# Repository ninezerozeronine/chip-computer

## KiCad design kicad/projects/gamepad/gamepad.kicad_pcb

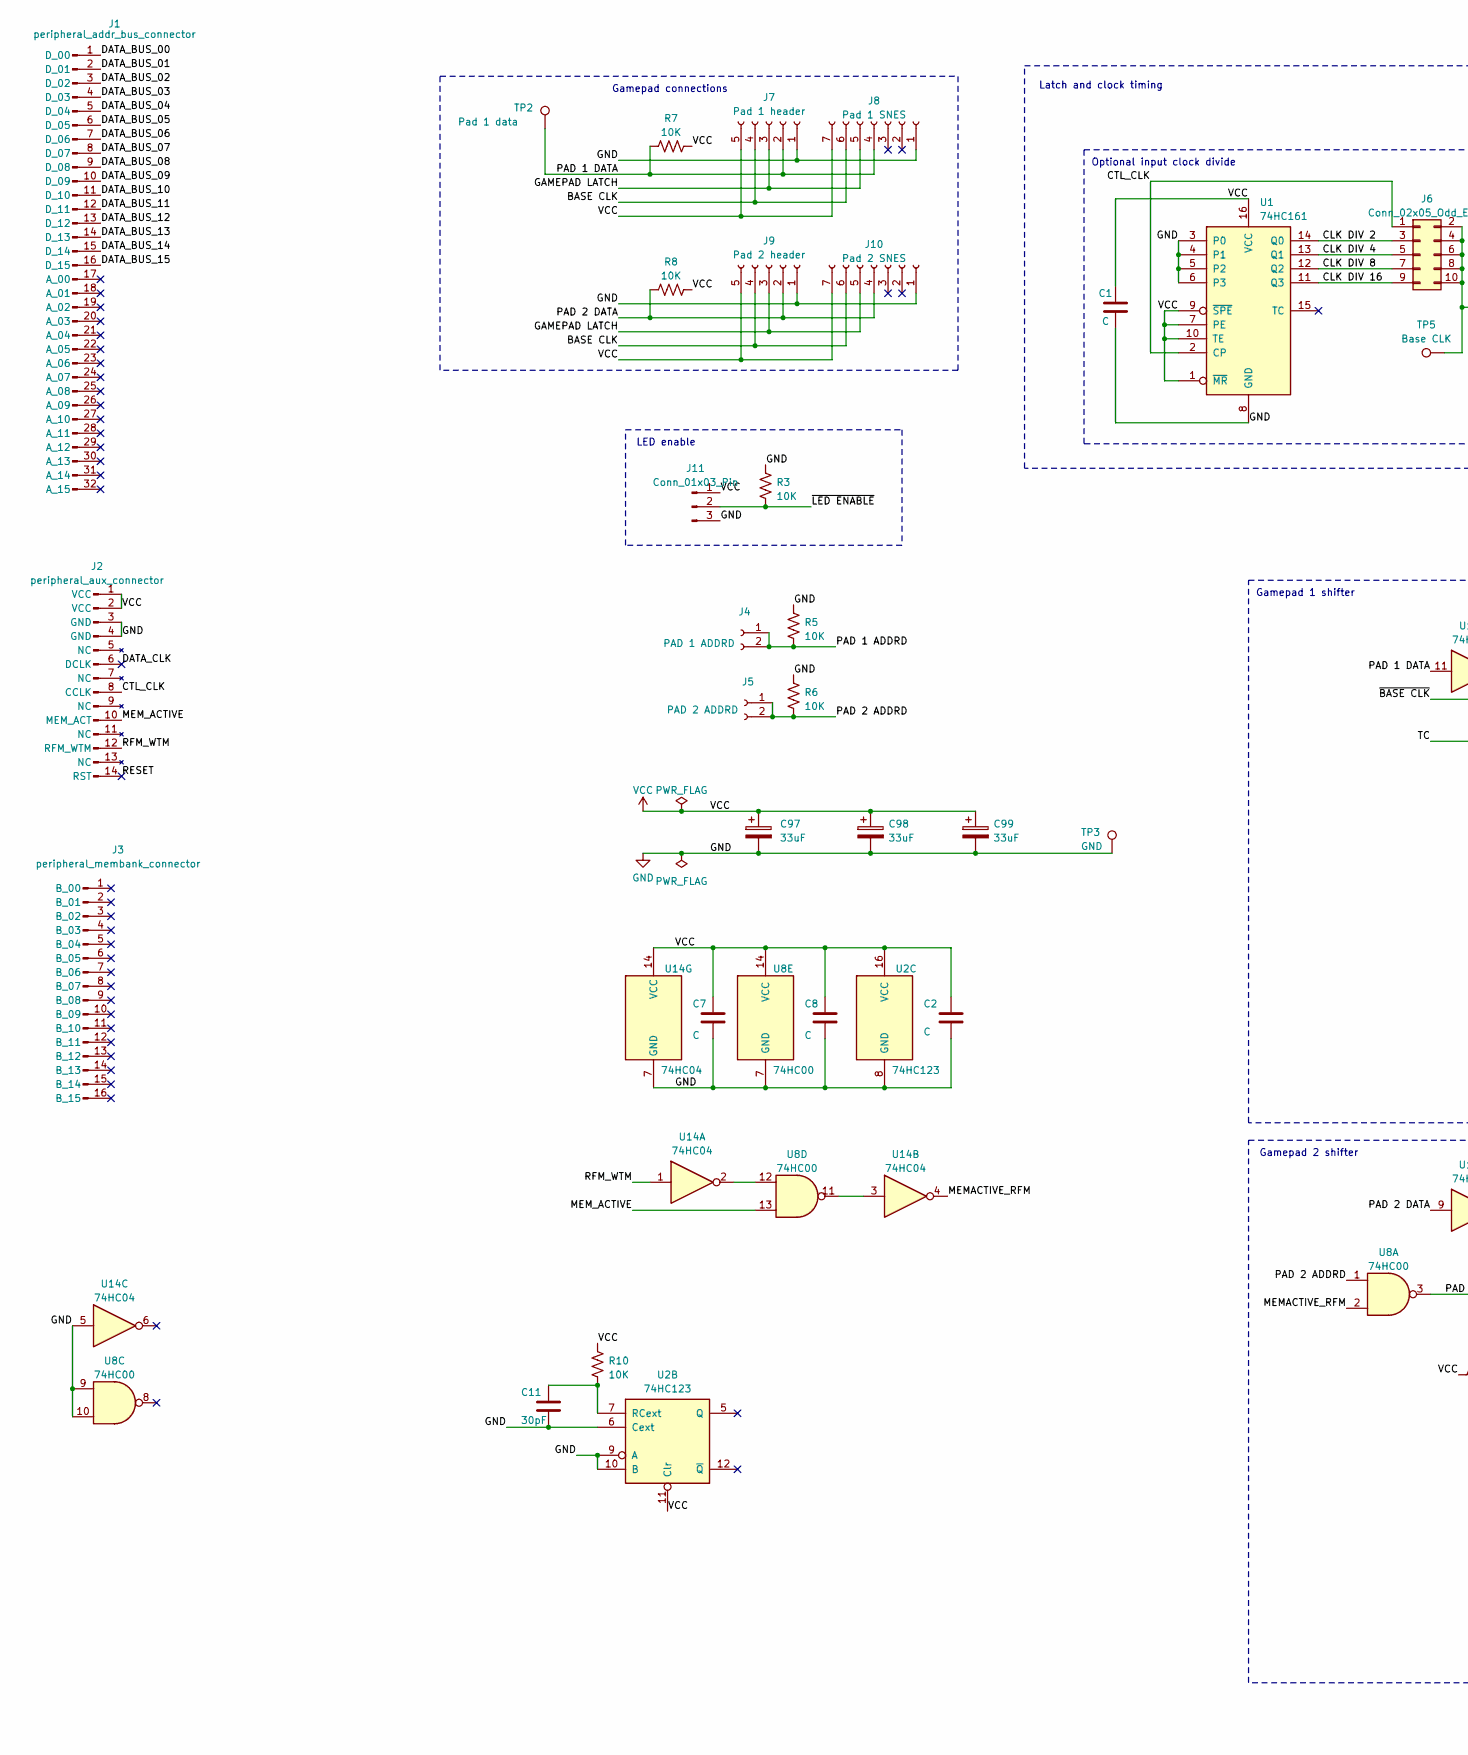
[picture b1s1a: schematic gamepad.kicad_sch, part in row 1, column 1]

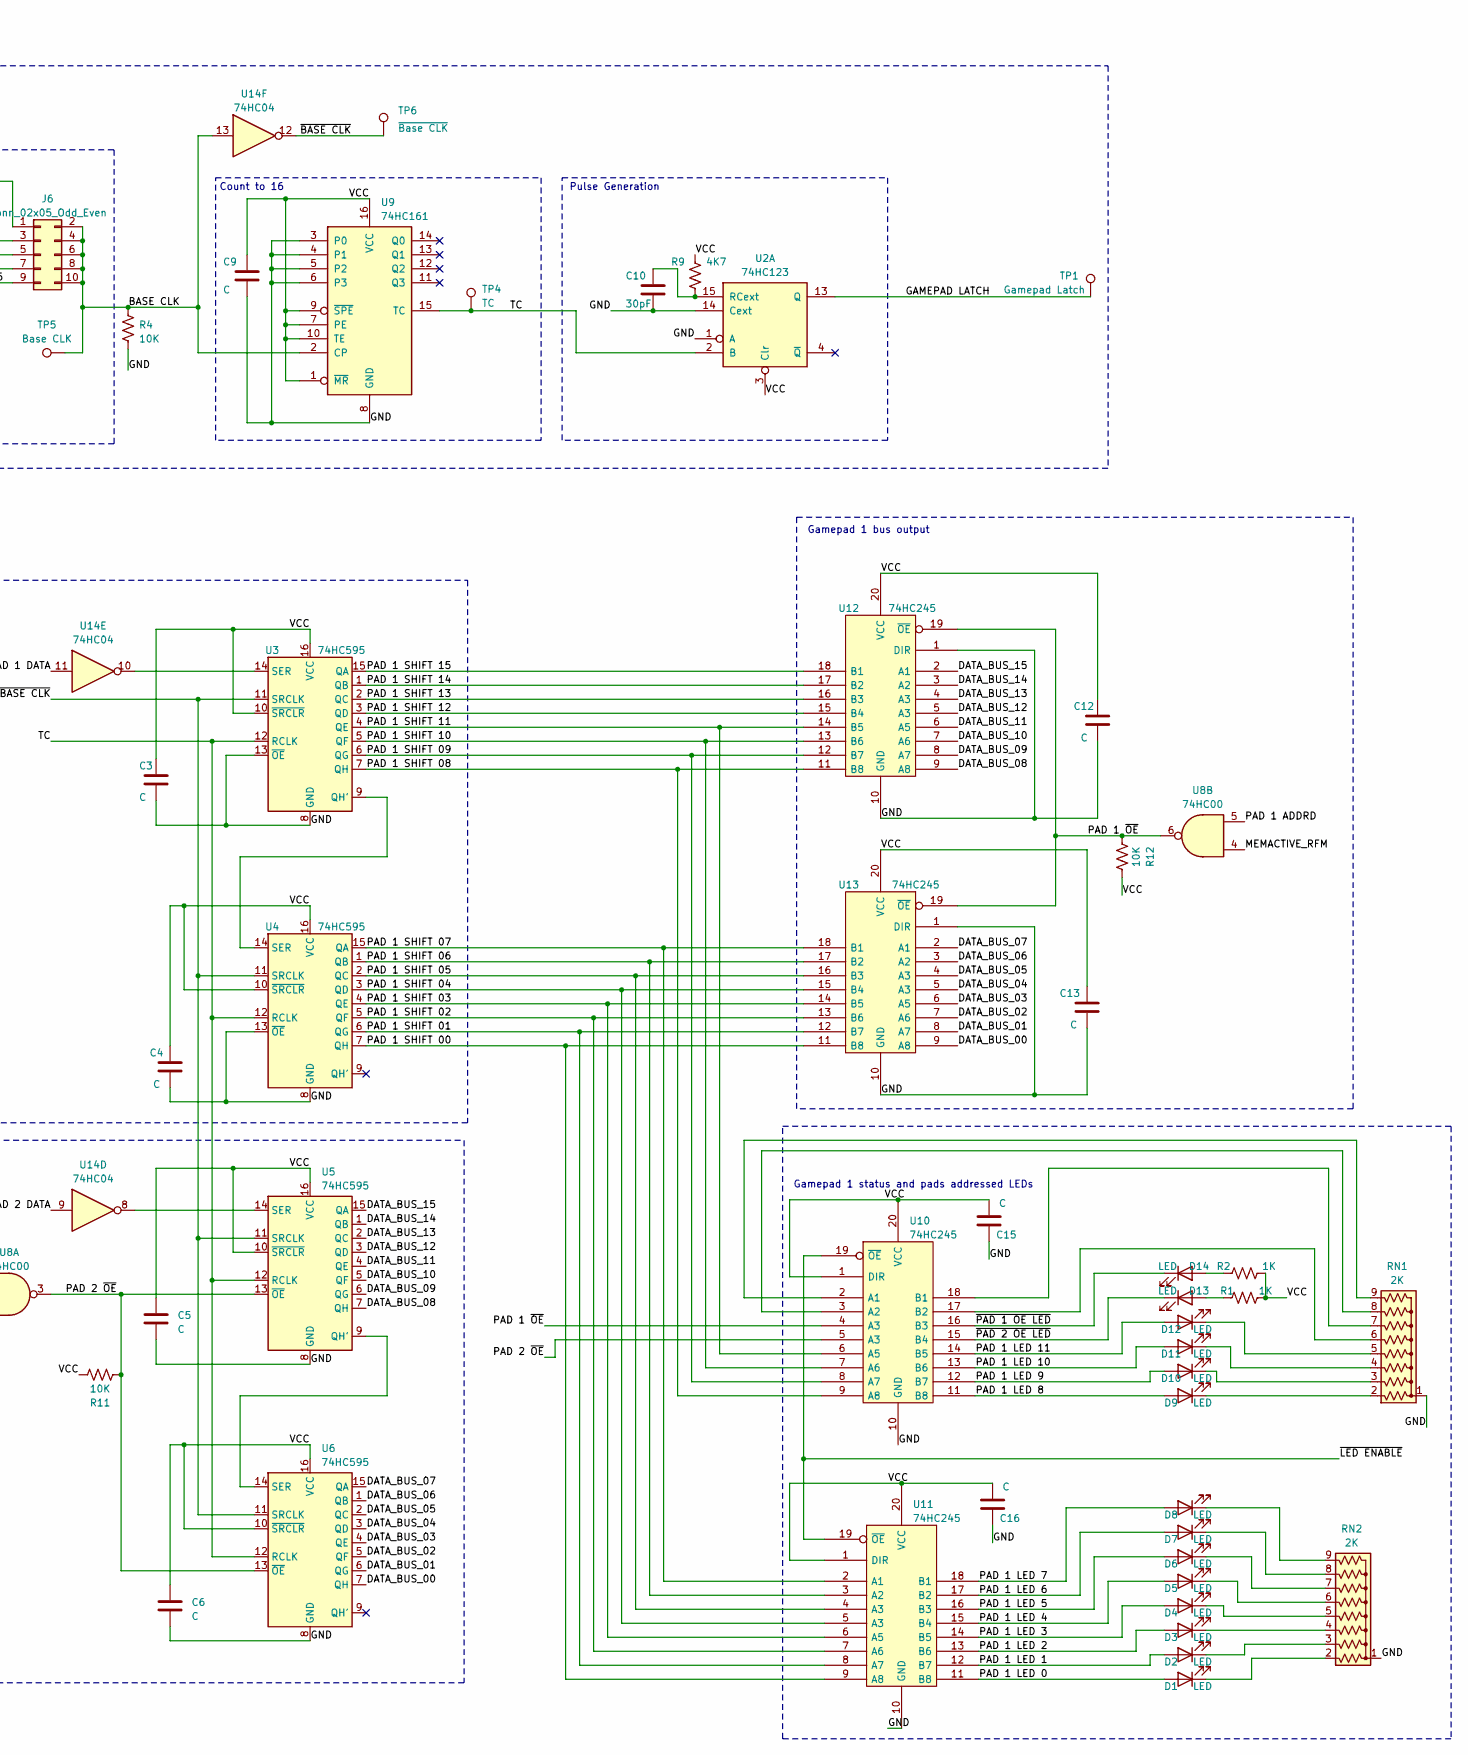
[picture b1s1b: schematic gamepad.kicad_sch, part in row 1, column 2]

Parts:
C1, C2, C3, C4, C5, C6, C7, C8, C9, C12, C13, C15, C16: C; C_Disc_D5.0mm_W2.5mm_P5.00mm
C10, C11: 30pF; C_Disc_D5.0mm_W2.5mm_P5.00mm
C97, C98, C99: 33uF; CP_Radial_D6.3mm_P2.50mm
D1, D2, D3, D4, D5, D6, D7, D8, D9, D10, D11, D12, D13, D14: LED; LED_D5.0mm_Horizontal_O3.81mm_Z3.0mm
J1: peripheral_addr_bus_connector; peripheral-backplane-data-addr-anno
J2: peripheral_aux_connector; peripheral-backplane-aux
J3: peripheral_membank_connector; peripheral-backplane-membank
J4: PAD 1 ADDRD; PinSocket_1x02_P2.54mm_Horizontal
J5: PAD 2 ADDRD; PinSocket_1x02_P2.54mm_Horizontal
J6: Conn_02x05_Odd_Even; PinHeader_2x05_P2.54mm_Vertical
J7: Pad 1 header; PinSocket_1x05_P2.54mm_Horizontal
J8: Pad 1 SNES; snes-rightangle-connector
J9: Pad 2 header; PinSocket_1x05_P2.54mm_Horizontal
J10: Pad 2 SNES; snes-rightangle-connector
J11: Conn_01x03_Pin; PinHeader_1x03_P2.54mm_Horizontal
R1, R2: 1K; R_Axial_DIN0207_L6.3mm_D2.5mm_P10.16mm_Horizontal
R3, R4, R5, R6, R7, R8, R10, R11, R12: 10K; R_Axial_DIN0207_L6.3mm_D2.5mm_P10.16mm_Horizontal
R9: 4K7; R_Axial_DIN0207_L6.3mm_D2.5mm_P10.16mm_Horizontal
RN1, RN2: 2K; R_Array_SIP9
TP1: Gamepad Latch; Pin_D1.0mm_L10.0mm
TP2: Pad 1 data; Pin_D1.0mm_L10.0mm
TP3: GND; Pin_D1.0mm_L10.0mm
TP4: TC; Pin_D1.0mm_L10.0mm
TP5: Base CLK; Pin_D1.0mm_L10.0mm
TP6: ~{Base CLK}; Pin_D1.0mm_L10.0mm
U1, U9: 74HC161; DIP-16_W7.62mm_Socket
U2: 74HC123; DIP-16_W7.62mm_Socket
U3, U4, U5, U6: 74HC595; DIP-16_W7.62mm_Socket
U8: 74HC00; DIP-14_W7.62mm_Socket
U10, U11, U12, U13: 74HC245; DIP-20_W7.62mm_Socket
U14: 74HC04; DIP-14_W7.62mm_Socket

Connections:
/BASE CLK: J6.2, J6.4, J6.6, J6.8, J6.10, J7.4, J8.6, J9.4, J10.6, R4.2, TP5.1, U9.2 (CP), U14.13
/CLK DIV 2: J6.3, U1.14 (Q0)
/CLK DIV 4: J6.5, U1.13 (Q1)
/CLK DIV 8: J6.7, U1.12 (Q2)
/CLK DIV 16: J6.9, U1.11 (Q3)
/CTL_CLK: J2.8 (CCLK), J6.1, U1.2 (CP)
/DATA_BUS_00: J1.1 (D_00), U6.7 (QH), U13.9 (A8)
/DATA_BUS_01: J1.2 (D_01), U6.6 (QG), U13.8 (A7)
/DATA_BUS_02: J1.3 (D_02), U6.5 (QF), U13.7 (A6)
/DATA_BUS_03: J1.4 (D_03), U6.4 (QE), U13.6 (A5)
/DATA_BUS_04: J1.5 (D_04), U6.3 (QD), U13.5 (A3)
/DATA_BUS_05: J1.6 (D_05), U6.2 (QC), U13.4 (A3)
/DATA_BUS_06: J1.7 (D_06), U6.1 (QB), U13.3 (A2)
/DATA_BUS_07: J1.8 (D_07), U6.15 (QA), U13.2 (A1)
/DATA_BUS_08: J1.9 (D_08), U5.7 (QH), U12.9 (A8)
/DATA_BUS_09: J1.10 (D_09), U5.6 (QG), U12.8 (A7)
/DATA_BUS_10: J1.11 (D_10), U5.5 (QF), U12.7 (A6)
/DATA_BUS_11: J1.12 (D_11), U5.4 (QE), U12.6 (A5)
/DATA_BUS_12: J1.13 (D_12), U5.3 (QD), U12.5 (A3)
/DATA_BUS_13: J1.14 (D_13), U5.2 (QC), U12.4 (A3)
/DATA_BUS_14: J1.15 (D_14), U5.1 (QB), U12.3 (A2)
/DATA_BUS_15: J1.16 (D_15), U5.15 (QA), U12.2 (A1)
/DATA_CLK: J2.6 (DCLK)
/GAMEPAD LATCH: J7.3, J8.5, J9.3, J10.5, TP1.1, U2.13 (Q)
/MEMACTIVE_RFM: U8.2, U8.4, U14.4
/MEM_ACTIVE: J2.10 (MEM_ACT), U8.13
/PAD 1 ADDRD: J4.1, J4.2, R5.1, U8.5
/PAD 1 DATA: J7.2, J8.4, R7.2, TP2.1, U14.11
/PAD 1 LED 0: D1.2 (A), U11.11 (B8)
/PAD 1 LED 1: D2.2 (A), U11.12 (B7)
/PAD 1 LED 2: D3.2 (A), U11.13 (B6)
/PAD 1 LED 3: D4.2 (A), U11.14 (B5)
/PAD 1 LED 4: D5.2 (A), U11.15 (B4)
/PAD 1 LED 5: D6.2 (A), U11.16 (B3)
/PAD 1 LED 6: D7.2 (A), U11.17 (B2)
/PAD 1 LED 7: D8.2 (A), U11.18 (B1)
/PAD 1 LED 8: D9.2 (A), U10.11 (B8)
/PAD 1 LED 9: D10.2 (A), U10.12 (B7)
/PAD 1 LED 10: D11.2 (A), U10.13 (B6)
/PAD 1 LED 11: D12.2 (A), U10.14 (B5)
/PAD 1 SHIFT 00: U4.7 (QH), U11.9 (A8), U13.11 (B8)
/PAD 1 SHIFT 01: U4.6 (QG), U11.8 (A7), U13.12 (B7)
/PAD 1 SHIFT 02: U4.5 (QF), U11.7 (A6), U13.13 (B6)
/PAD 1 SHIFT 03: U4.4 (QE), U11.6 (A5), U13.14 (B5)
/PAD 1 SHIFT 04: U4.3 (QD), U11.5 (A3), U13.15 (B4)
/PAD 1 SHIFT 05: U4.2 (QC), U11.4 (A3), U13.16 (B3)
/PAD 1 SHIFT 06: U4.1 (QB), U11.3 (A2), U13.17 (B2)
/PAD 1 SHIFT 07: U4.15 (QA), U11.2 (A1), U13.18 (B1)
/PAD 1 SHIFT 08: U3.7 (QH), U10.9 (A8), U12.11 (B8)
/PAD 1 SHIFT 09: U3.6 (QG), U10.8 (A7), U12.12 (B7)
/PAD 1 SHIFT 10: U3.5 (QF), U10.7 (A6), U12.13 (B6)
/PAD 1 SHIFT 11: U3.4 (QE), U10.6 (A5), U12.14 (B5)
/PAD 1 SHIFT 12: U3.3 (QD), U12.15 (B4)
/PAD 1 SHIFT 13: U3.2 (QC), U12.16 (B3)
/PAD 1 SHIFT 14: U3.1 (QB), U12.17 (B2)
/PAD 1 SHIFT 15: U3.15 (QA), U12.18 (B1)
/PAD 1 ~OE: R12.2, U8.6, U10.4 (A3), U12.19 (~OE), U13.19 (~OE)
/PAD 2 ADDRD: J5.1, J5.2, R6.1, U8.1
/PAD 2 DATA: J9.2, J10.4, R8.2, U14.9
/PAD 2 ~OE: R11.2, U5.13 (~OE), U6.13 (~OE), U8.3, U10.5 (A3)
/RESET: J2.14 (RST)
/RFM_WTM: J2.12 (RFM_WTM), U14.1
/TC: TP4.1, U2.2 (B), U3.12 (RCLK), U4.12 (RCLK), U5.12 (RCLK), U6.12 (RCLK), U9.15 (TC)
/~BASE CLK: TP6.1, U3.11 (SRCLK), U4.11 (SRCLK), U5.11 (SRCLK), U6.11 (SRCLK), U14.12
/~LED ENABLE: J11.2, R3.1, U10.19 (~OE), U11.19 (~OE)
/~PAD 1 OE LED: D14.1 (K), U10.16 (B3)
/~PAD 2 OE LED: D13.1 (K), U10.15 (B4)
GND: C1.2, C2.2, C3.2, C4.2, C5.2, C6.2, C7.2, C8.2, C9.2, C10.2, C11.2, C12.2, C13.2, C15.1, C16.1, C97.2, C98.2, C99.2, J2.3 (GND), J2.4 (GND), J7.1, J8.1, J9.1, J10.1, J11.3, R3.2, R4.1, R5.2, R6.2, RN1.1 (common), RN2.1 (common), TP3.1, U1.3 (P0), U1.4 (P1), U1.5 (P2), U1.6 (P3), U1.8 (GND), U2.1 (A), U2.6 (Cext), U2.8 (GND), U2.9 (A), U2.10 (B), U2.14 (Cext), U3.8 (GND), U3.13 (~OE), U4.8 (GND), U4.13 (~OE), U5.8 (GND), U6.8 (GND), U8.7 (GND), U8.9, U8.10, U9.3 (P0), U9.4 (P1), U9.5 (P2), U9.6 (P3), U9.8 (GND), U10.10 (GND), U11.10 (GND), U12.1 (DIR), U12.10 (GND), U13.1 (DIR), U13.10 (GND), U14.5, U14.7 (GND)
unnamed: D1.1 (K), RN2.2 (R1)
unnamed: D2.1 (K), RN2.3 (R2)
unnamed: D3.1 (K), RN2.4 (R3)
unnamed: D4.1 (K), RN2.5 (R4)
unnamed: D5.1 (K), RN2.6 (R5)
unnamed: D6.1 (K), RN2.7 (R6)
unnamed: D7.1 (K), RN2.8 (R7)
unnamed: D8.1 (K), RN2.9 (R8)
unnamed: D9.1 (K), RN1.2 (R1)
unnamed: D10.1 (K), RN1.3 (R2)
unnamed: D11.1 (K), RN1.4 (R3)
unnamed: D12.1 (K), RN1.5 (R4)
unnamed: D13.2 (A), R1.1
unnamed: D14.2 (A), R2.1
unnamed: RN1.6 (R5), U10.17 (B2)
unnamed: RN1.7 (R6), U10.18 (B1)
unnamed: RN1.8 (R7), U10.3 (A2)
unnamed: RN1.9 (R8), U10.2 (A1)
unnamed: C10.1, R9.1, U2.15 (RCext)
unnamed: C11.1, R10.1, U2.7 (RCext)
unnamed: U3.9 (QH'), U4.14 (SER)
unnamed: U3.14 (SER), U14.10
unnamed: U5.9 (QH'), U6.14 (SER)
unnamed: U5.14 (SER), U14.8
unnamed: U8.12, U14.2
unnamed: U8.11, U14.3
VCC: C1.1, C2.1, C3.1, C4.1, C5.1, C6.1, C7.1, C8.1, C9.1, C12.1, C13.1, C15.2, C16.2, C97.1, C98.1, C99.1, J2.1 (VCC), J2.2 (VCC), J7.5, J8.7, J9.5, J10.7, J11.1, R1.2, R2.2, R7.1, R8.1, R9.2, R10.2, R11.1, R12.1, U1.1 (~MR), U1.7 (PE), U1.9 (~SPE), U1.10 (TE), U1.16 (VCC), U2.3 (Clr), U2.11 (Clr), U2.16 (VCC), U3.10 (~SRCLR), U3.16 (VCC), U4.10 (~SRCLR), U4.16 (VCC), U5.10 (~SRCLR), U5.16 (VCC), U6.10 (~SRCLR), U6.16 (VCC), U8.14 (VCC), U9.1 (~MR), U9.7 (PE), U9.9 (~SPE), U9.10 (TE), U9.16 (VCC), U10.1 (DIR), U10.20 (VCC), U11.1 (DIR), U11.20 (VCC), U12.20 (VCC), U13.20 (VCC), U14.14 (VCC)

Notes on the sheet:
Count to 16
Pulse Generation
Gamepad 1 shifter
LED enable
Optional input clock divide
Gamepad connections
Latch and clock timing
Gamepad 1 status and pads addressed LEDs
Gamepad 2 shifter
Gamepad 1 bus output

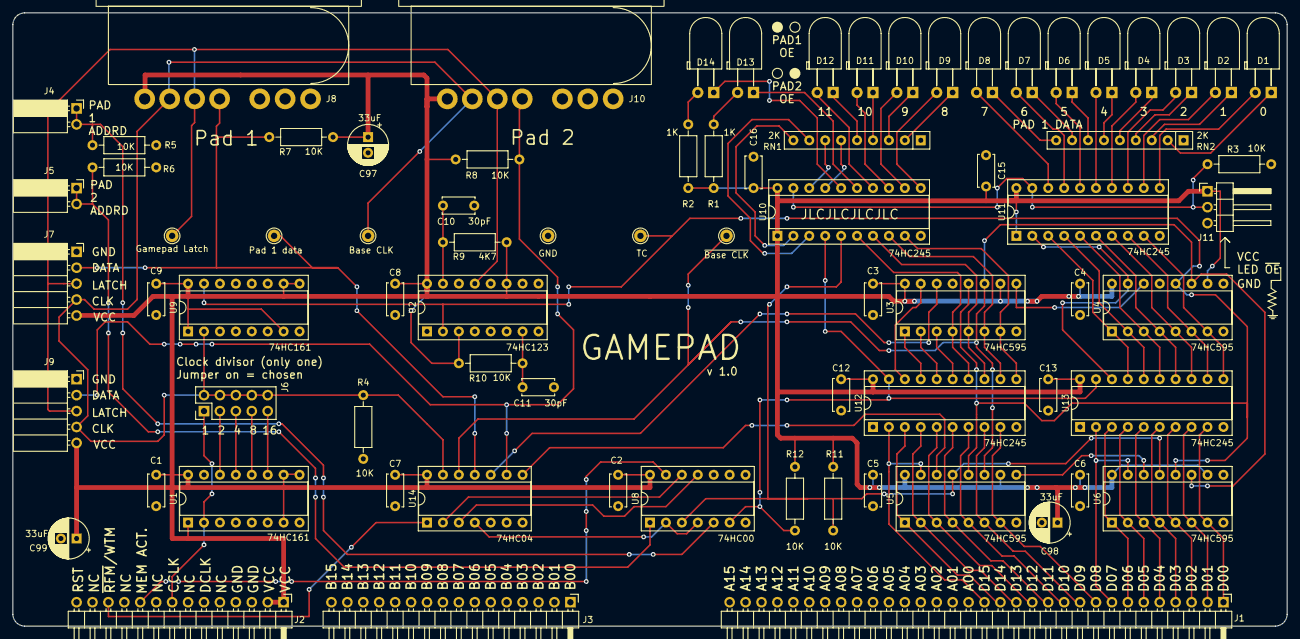
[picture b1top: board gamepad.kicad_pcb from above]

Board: 2 copper layers, 203.2 x 97.8 mm, 76 parts (0 on the bottom side), 93 nets.

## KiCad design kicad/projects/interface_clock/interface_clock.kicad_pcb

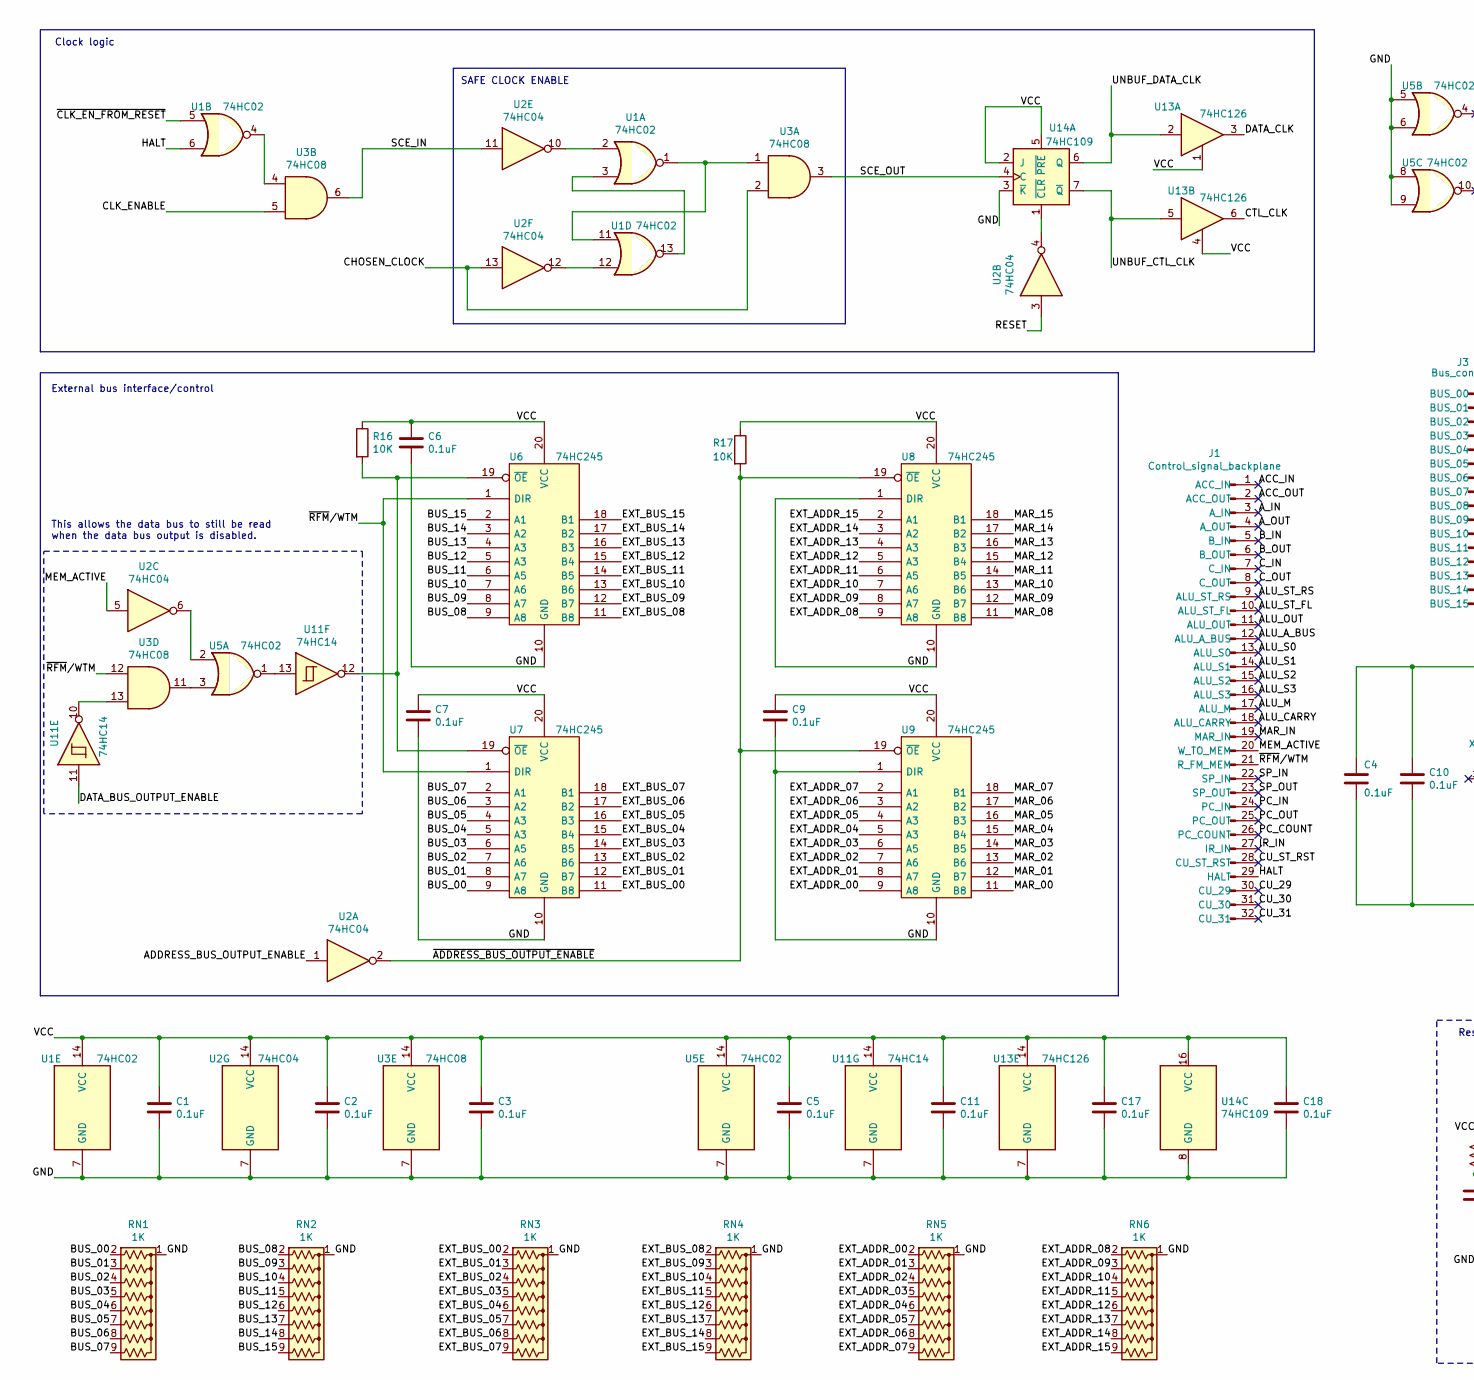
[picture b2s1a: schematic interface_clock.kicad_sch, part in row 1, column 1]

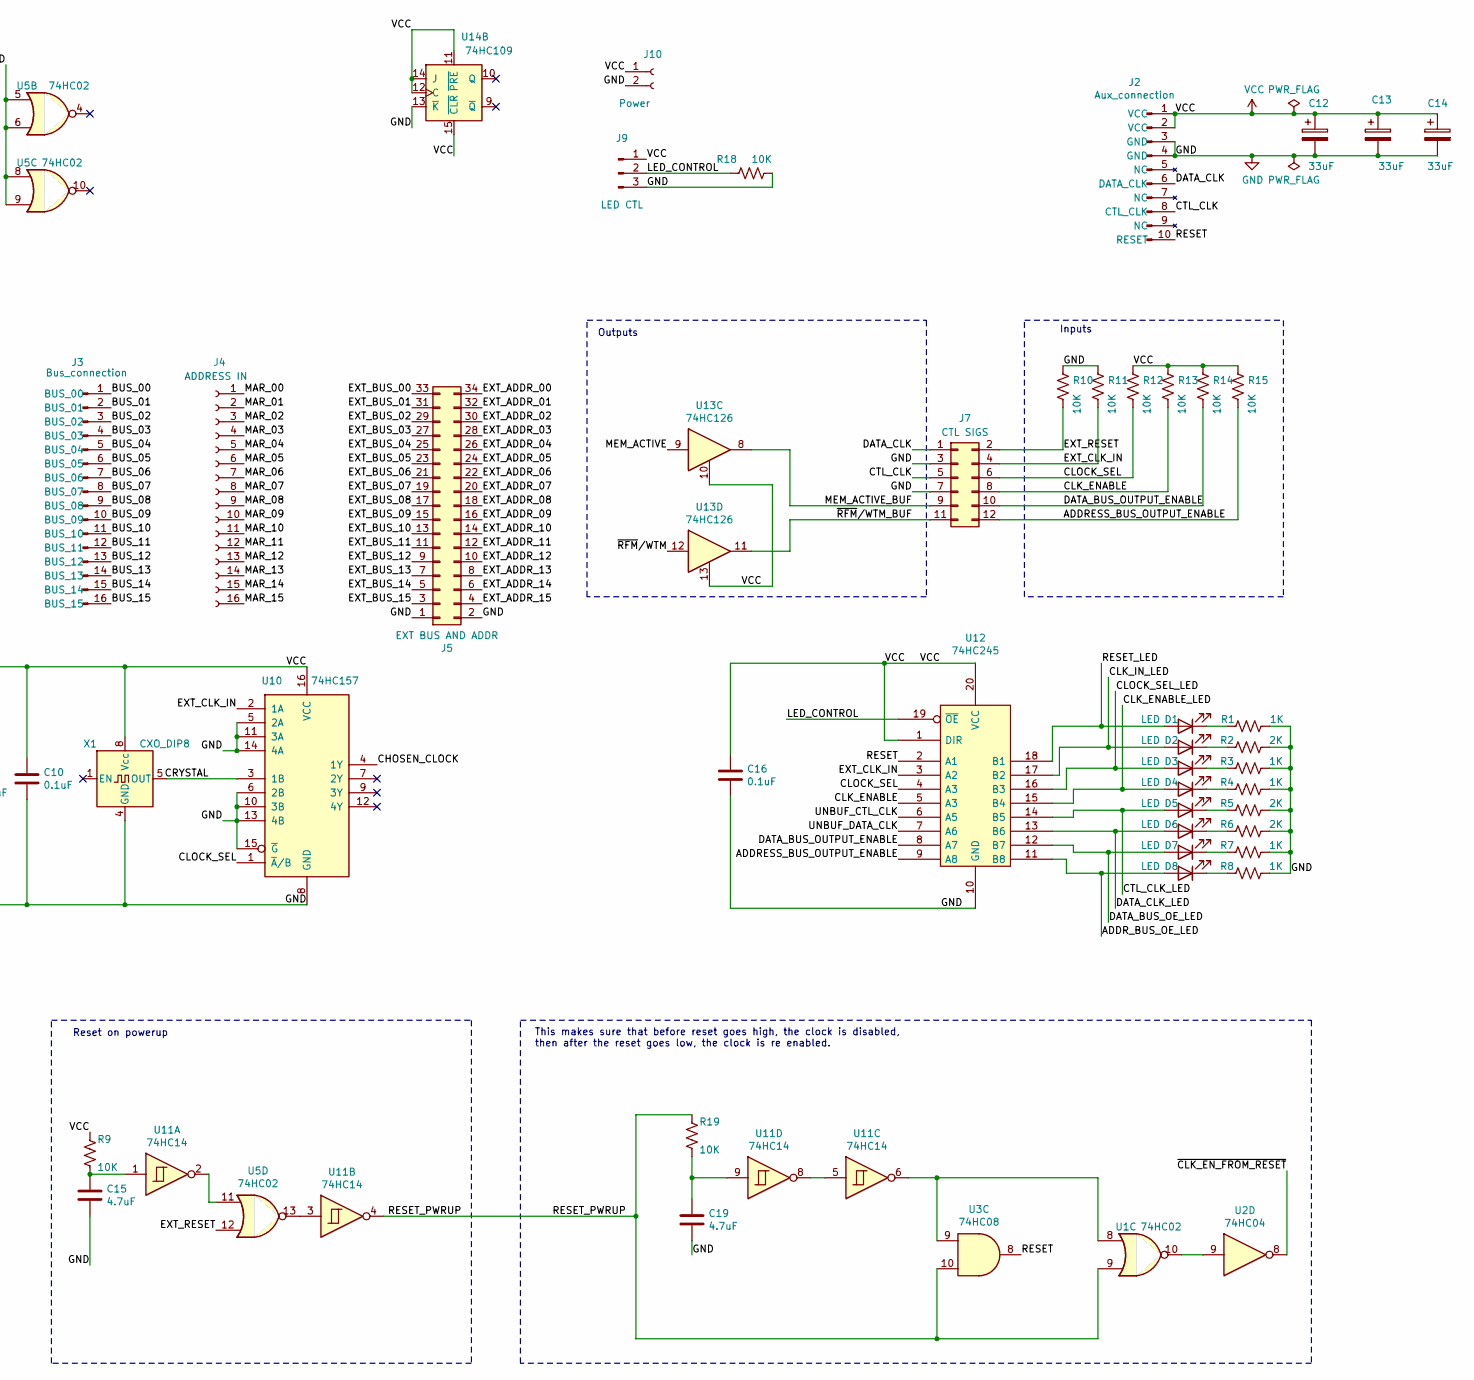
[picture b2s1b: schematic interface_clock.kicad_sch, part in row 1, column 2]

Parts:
C1, C2, C3, C4, C5, C6, C7, C9, C10, C11, C16, C17, C18: 0.1uF; C_Disc_D4.7mm_W2.5mm_P5.00mm
C12, C13, C14: 33uF; CP_Radial_D6.3mm_P2.50mm
C15, C19: 4.7uF; C_Disc_D4.7mm_W2.5mm_P5.00mm
D1, D2, D3, D4, D5, D6, D7, D8: LED; LED_D5.0mm_Horizontal_O3.81mm_Z3.0mm
J1: Control_signal_backplane; backplane-connector-single-row-annotated
J2: Aux_connection; aux-connection
J3: Bus_connection; bus-connection
J4: ADDRESS IN; PinSocket_1x16_P2.54mm_Horizontal
J5: EXT BUS AND ADDR; PinSocket_2x17_P2.54mm_Horizontal
J7: CTL SIGS; PinSocket_2x06_P2.54mm_Horizontal
J9: LED CTL; PinHeader_1x03_P2.54mm_Horizontal
J10: Power; PinSocket_1x02_P2.54mm_Horizontal
R1, R3, R4, R7, R8: 1K; R_Axial_DIN0207_L6.3mm_D2.5mm_P10.16mm_Horizontal
R2, R5, R6: 2K; R_Axial_DIN0207_L6.3mm_D2.5mm_P10.16mm_Horizontal
R9, R10, R11, R12, R13, R14, R15, R16, R17, R18, R19: 10K; R_Axial_DIN0207_L6.3mm_D2.5mm_P10.16mm_Horizontal
RN1, RN2, RN3, RN4, RN5, RN6: 1K; R_Array_SIP9
U1, U5: 74HC02; DIP-14_W7.62mm_Socket
U2: 74HC04; DIP-14_W7.62mm_Socket
U3: 74HC08; DIP-14_W7.62mm_Socket
U6, U7, U8, U9, U12: 74HC245; DIP-20_W7.62mm_Socket
U10: 74HC157; DIP-16_W7.62mm_Socket
U11: 74HC14; DIP-14_W7.62mm_Socket
U13: 74HC126; DIP-14_W7.62mm_Socket
U14: 74HC109; DIP-16_W7.62mm_Socket
X1: CXO_DIP8; Oscillator_DIP-8

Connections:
/ACC_IN: J1.1 (ACC_IN)
/ACC_OUT: J1.2 (ACC_OUT)
/ADDRESS_BUS_OUTPUT_ENABLE: J7.12, R15.2, U2.1, U12.9 (A8)
/ADDR_BUS_OE_LED: D8.2 (A), U12.11 (B8)
/ALU_A_BUS: J1.12 (ALU_A_BUS)
/ALU_CARRY: J1.18 (ALU_CARRY)
/ALU_M: J1.17 (ALU_M)
/ALU_OUT: J1.11 (ALU_OUT)
/ALU_S0: J1.13 (ALU_S0)
/ALU_S1: J1.14 (ALU_S1)
/ALU_S2: J1.15 (ALU_S2)
/ALU_S3: J1.16 (ALU_S3)
/ALU_ST_FL: J1.10 (ALU_ST_FL)
/ALU_ST_RS: J1.9 (ALU_ST_RS)
/A_IN: J1.3 (A_IN)
/A_OUT: J1.4 (A_OUT)
/BUS_00: J3.1 (BUS_00), RN1.2 (R1), U7.9 (A8)
/BUS_01: J3.2 (BUS_01), RN1.3 (R2), U7.8 (A7)
/BUS_02: J3.3 (BUS_02), RN1.4 (R3), U7.7 (A6)
/BUS_03: J3.4 (BUS_03), RN1.5 (R4), U7.6 (A5)
/BUS_04: J3.5 (BUS_04), RN1.6 (R5), U7.5 (A3)
/BUS_05: J3.6 (BUS_05), RN1.7 (R6), U7.4 (A3)
/BUS_06: J3.7 (BUS_06), RN1.8 (R7), U7.3 (A2)
/BUS_07: J3.8 (BUS_07), RN1.9 (R8), U7.2 (A1)
/BUS_08: J3.9 (BUS_08), RN2.2 (R1), U6.9 (A8)
/BUS_09: J3.10 (BUS_09), RN2.3 (R2), U6.8 (A7)
/BUS_10: J3.11 (BUS_10), RN2.4 (R3), U6.7 (A6)
/BUS_11: J3.12 (BUS_11), RN2.5 (R4), U6.6 (A5)
/BUS_12: J3.13 (BUS_12), RN2.6 (R5), U6.5 (A3)
/BUS_13: J3.14 (BUS_13), RN2.7 (R6), U6.4 (A3)
/BUS_14: J3.15 (BUS_14), RN2.8 (R7), U6.3 (A2)
/BUS_15: J3.16 (BUS_15), RN2.9 (R8), U6.2 (A1)
/B_IN: J1.5 (B_IN)
/B_OUT: J1.6 (B_OUT)
/CHOSEN_CLOCK: U2.13, U3.2, U10.4 (1Y)
/CLK_ENABLE: J7.8, R13.2, U3.5, U12.5 (A3)
/CLK_ENABLE_LED: D4.2 (A), U12.15 (B4)
/CLK_IN_LED: D2.2 (A), U12.17 (B2)
/CLOCK_SEL: J7.6, R12.2, U10.1 (~A/B), U12.4 (A3)
/CLOCK_SEL_LED: D3.2 (A), U12.16 (B3)
/CRYSTAL: U10.3 (1B), X1.5 (OUT)
/CTL_CLK: J2.8 (CTL_CLK), J7.5, U13.6
/CTL_CLK_LED: D5.2 (A), U12.14 (B5)
/CU_29: J1.30 (CU_29)
/CU_30: J1.31 (CU_30)
/CU_31: J1.32 (CU_31)
/CU_ST_RST: J1.28 (CU_ST_RST)
/C_IN: J1.7 (C_IN)
/C_OUT: J1.8 (C_OUT)
/DATA_BUS_OE_LED: D7.2 (A), U12.12 (B7)
/DATA_BUS_OUTPUT_ENABLE: J7.10, R14.2, U11.11, U12.8 (A7)
/DATA_CLK: J2.6 (DATA_CLK), J7.1, U13.3
/DATA_CLK_LED: D6.2 (A), U12.13 (B6)
/EXT_ADDR_00: J5.34, RN5.2 (R1), U9.9 (A8)
/EXT_ADDR_01: J5.32, RN5.3 (R2), U9.8 (A7)
/EXT_ADDR_02: J5.30, RN5.4 (R3), U9.7 (A6)
/EXT_ADDR_03: J5.28, RN5.5 (R4), U9.6 (A5)
/EXT_ADDR_04: J5.26, RN5.6 (R5), U9.5 (A3)
/EXT_ADDR_05: J5.24, RN5.7 (R6), U9.4 (A3)
/EXT_ADDR_06: J5.22, RN5.8 (R7), U9.3 (A2)
/EXT_ADDR_07: J5.20, RN5.9 (R8), U9.2 (A1)
/EXT_ADDR_08: J5.18, RN6.2 (R1), U8.9 (A8)
/EXT_ADDR_09: J5.16, RN6.3 (R2), U8.8 (A7)
/EXT_ADDR_10: J5.14, RN6.4 (R3), U8.7 (A6)
/EXT_ADDR_11: J5.12, RN6.5 (R4), U8.6 (A5)
/EXT_ADDR_12: J5.10, RN6.6 (R5), U8.5 (A3)
/EXT_ADDR_13: J5.8, RN6.7 (R6), U8.4 (A3)
/EXT_ADDR_14: J5.6, RN6.8 (R7), U8.3 (A2)
/EXT_ADDR_15: J5.4, RN6.9 (R8), U8.2 (A1)
/EXT_BUS_00: J5.33, RN3.2 (R1), U7.11 (B8)
/EXT_BUS_01: J5.31, RN3.3 (R2), U7.12 (B7)
/EXT_BUS_02: J5.29, RN3.4 (R3), U7.13 (B6)
/EXT_BUS_03: J5.27, RN3.5 (R4), U7.14 (B5)
/EXT_BUS_04: J5.25, RN3.6 (R5), U7.15 (B4)
/EXT_BUS_05: J5.23, RN3.7 (R6), U7.16 (B3)
/EXT_BUS_06: J5.21, RN3.8 (R7), U7.17 (B2)
/EXT_BUS_07: J5.19, RN3.9 (R8), U7.18 (B1)
/EXT_BUS_08: J5.17, RN4.2 (R1), U6.11 (B8)
/EXT_BUS_09: J5.15, RN4.3 (R2), U6.12 (B7)
/EXT_BUS_10: J5.13, RN4.4 (R3), U6.13 (B6)
/EXT_BUS_11: J5.11, RN4.5 (R4), U6.14 (B5)
/EXT_BUS_12: J5.9, RN4.6 (R5), U6.15 (B4)
/EXT_BUS_13: J5.7, RN4.7 (R6), U6.16 (B3)
/EXT_BUS_14: J5.5, RN4.8 (R7), U6.17 (B2)
/EXT_BUS_15: J5.3, RN4.9 (R8), U6.18 (B1)
/EXT_CLK_IN: J7.4, R11.2, U10.2 (1A), U12.3 (A2)
/EXT_RESET: J7.2, R10.2, U5.12
/HALT: J1.29 (HALT), U1.6
/IR_IN: J1.27 (IR_IN)
/LED_CONTROL: J9.2, R18.1, U12.19 (~OE)
/MAR_00: J4.1, U9.11 (B8)
/MAR_01: J4.2, U9.12 (B7)
/MAR_02: J4.3, U9.13 (B6)
/MAR_03: J4.4, U9.14 (B5)
/MAR_04: J4.5, U9.15 (B4)
/MAR_05: J4.6, U9.16 (B3)
/MAR_06: J4.7, U9.17 (B2)
/MAR_07: J4.8, U9.18 (B1)
/MAR_08: J4.9, U8.11 (B8)
/MAR_09: J4.10, U8.12 (B7)
/MAR_10: J4.11, U8.13 (B6)
/MAR_11: J4.12, U8.14 (B5)
/MAR_12: J4.13, U8.15 (B4)
/MAR_13: J4.14, U8.16 (B3)
/MAR_14: J4.15, U8.17 (B2)
/MAR_15: J4.16, U8.18 (B1)
/MAR_IN: J1.19 (MAR_IN)
/MEM_ACTIVE: J1.20 (W_TO_MEM), U2.5, U13.9
/MEM_ACTIVE_BUF: J7.9, U13.8
/PC_COUNT: J1.26 (PC_COUNT)
/PC_IN: J1.24 (PC_IN)
/PC_OUT: J1.25 (PC_OUT)
/RESET: J2.10 (RESET), U2.3, U3.8, U12.2 (A1)
/RESET_LED: D1.2 (A), U12.18 (B1)
/RESET_PWRUP: R19.1, U1.9, U3.10, U11.4
/SCE_IN: U2.11, U3.6
/SCE_OUT: U3.3, U14.4 (C)
/SP_IN: J1.22 (SP_IN)
/SP_OUT: J1.23 (SP_OUT)
/UNBUF_CTL_CLK: U12.6 (A5), U13.5, U14.7 (~Q)
/UNBUF_DATA_CLK: U12.7 (A6), U13.2, U14.6 (Q)
/~ADDRESS_BUS_OUTPUT_ENABLE: R17.2, U2.2, U8.19 (~OE), U9.19 (~OE)
/~CLK_EN_FROM_RESET: U1.5, U2.8
/~RFM/WTM: J1.21 (R_FM_MEM), U3.12, U6.1 (DIR), U7.1 (DIR), U13.12
/~RFM/WTM_BUF: J7.11, U13.11
GND: C1.1, C2.2, C3.2, C4.2, C5.2, C6.2, C7.2, C9.2, C10.2, C11.2, C12.2, C13.2, C14.2, C15.2, C16.2, C17.2, C18.2, C19.2, J2.3 (GND), J2.4 (GND), J5.1, J5.2, J7.3, J7.7, J9.3, J10.2, R1.1, R2.2, R3.2, R4.2, R5.2, R6.2, R7.2, R8.2, R10.1, R11.1, R18.2, RN1.1 (common), RN2.1 (common), RN3.1 (common), RN4.1 (common), RN5.1 (common), RN6.1 (common), U1.7 (GND), U2.7 (GND), U3.7 (GND), U5.5, U5.6, U5.7 (GND), U5.8, U5.9, U6.10 (GND), U7.10 (GND), U8.1 (DIR), U8.10 (GND), U9.1 (DIR), U9.10 (GND), U10.5 (2A), U10.6 (2B), U10.8 (GND), U10.10 (3B), U10.11 (3A), U10.13 (4B), U10.14 (4A), U10.15 (~G), U11.7 (GND), U12.10 (GND), U13.7 (GND), U14.3 (~K), U14.8 (GND), U14.13 (~K), X1.4 (GND)
unnamed: C15.1, R9.2, U11.1
unnamed: C19.1, R19.2, U11.9
unnamed: D1.1 (K), R1.2
unnamed: D2.1 (K), R2.1
unnamed: D3.1 (K), R3.1
unnamed: D4.1 (K), R4.1
unnamed: D5.1 (K), R5.1
unnamed: D6.1 (K), R6.1
unnamed: D7.1 (K), R7.1
unnamed: D8.1 (K), R8.1
unnamed: U1.1, U1.11, U3.1
unnamed: U1.2, U2.10
unnamed: U1.4, U3.4
unnamed: U1.8, U3.9, U11.6
unnamed: U1.10, U2.9
unnamed: U1.12, U2.12
unnamed: U1.3, U1.13
unnamed: U2.6, U5.2
unnamed: U3.11, U5.3
unnamed: R16.2, U6.19 (~OE), U7.19 (~OE), U11.12
unnamed: U5.11, U11.2
unnamed: U5.13, U11.3
unnamed: U11.5, U11.8
unnamed: U3.13, U11.10
unnamed: U5.1, U11.13
unnamed: U2.4, U14.1 (~CLR)
VCC: C1.2, C2.1, C3.1, C4.1, C5.1, C6.1, C7.1, C9.1, C10.1, C11.1, C12.1, C13.1, C14.1, C16.1, C17.1, C18.1, J2.1 (VCC), J2.2 (VCC), J9.1, J10.1, R9.1, R12.1, R13.1, R14.1, R15.1, R16.1, R17.1, U1.14 (VCC), U2.14 (VCC), U3.14 (VCC), U5.14 (VCC), U6.20 (VCC), U7.20 (VCC), U8.20 (VCC), U9.20 (VCC), U10.16 (VCC), U11.14 (VCC), U12.1 (DIR), U12.20 (VCC), U13.1, U13.4, U13.10, U13.13, U13.14 (VCC), U14.2 (J), U14.5 (~PRE), U14.11 (~PRE), U14.12 (C), U14.14 (J), U14.15 (~CLR), U14.16 (VCC), X1.8 (Vcc)

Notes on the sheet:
Inputs
This makes sure that before reset goes high, the clock is disabled, then after the reset goes low, the clock is re enabled.
This allows the data bus to still be read when the data bus output is disabled.
Reset on powerup
SAFE CLOCK ENABLE
Clock logic
Outputs
External bus interface/control

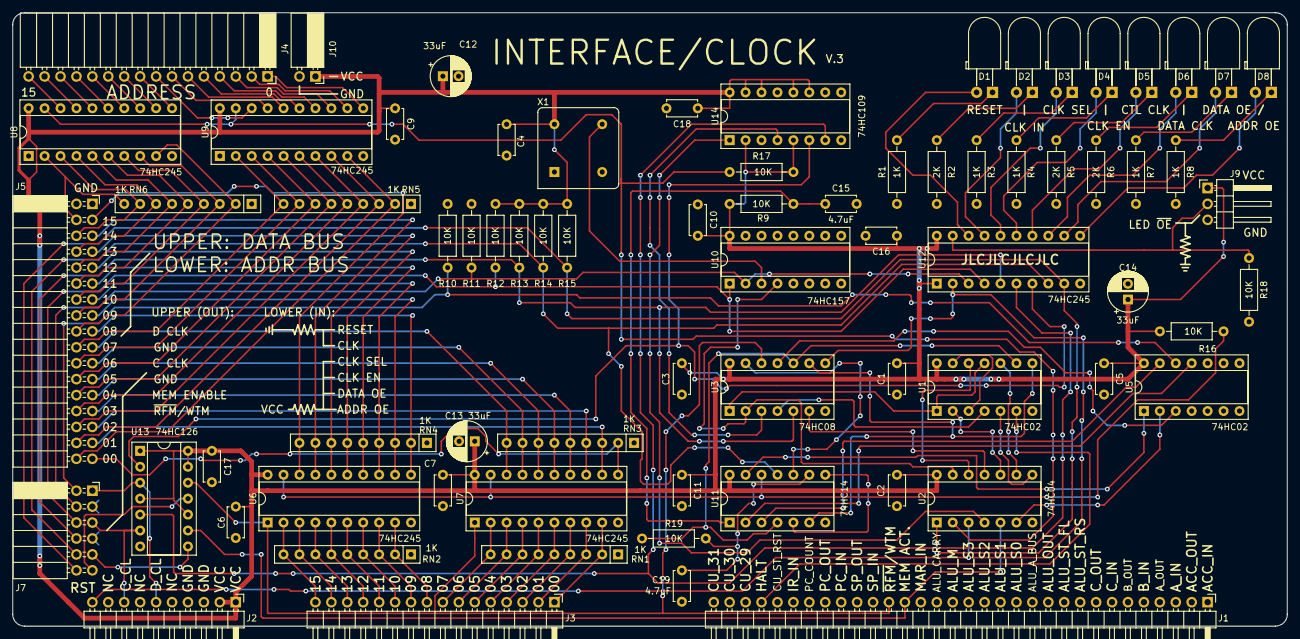
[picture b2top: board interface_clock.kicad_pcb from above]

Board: 2 copper layers, 203.2 x 97.8 mm, 73 parts (0 on the bottom side), 124 nets.
